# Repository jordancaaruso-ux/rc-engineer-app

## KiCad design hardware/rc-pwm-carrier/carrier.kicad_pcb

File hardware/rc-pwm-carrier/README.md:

# RC PWM Logger — Carrier Board (rev A)

Small carrier PCB for the **ESP32-S3-DevKitC-1** dev board. The devkit plugs into two
socket rows; the carrier provides receiver-rail power, PWM voltage dividers, and
servo-lead connectors. Replaces the loose-wire prototype in
`../rc-pwm-logger/PROTOTYPE_BUILD_PACKET.md` with a track-worthy, JLCPCB-assembled board.

**This is NOT the full custom board** — that project (`../rc-pwm-logger/V1.*`) is parked.
The carrier exists to prove the passive-tap concept and the data's value cheaply.

## Locked decisions (founder, 2026-07-18)

| Decision | Choice |
|---|---|
| Compute | ESP32-S3-DevKitC-1 (USB-C, WROOM-1 N8) — plugs in, never soldered |
| Power | From the receiver/BEC rail (5.5–8.4 V) via on-board buck to 5 V |
| Channels | 2 — steering + throttle/brake, standard 3-pin servo headers |
| Assembly | JLCPCB assembles everything incl. through-hole (founder does zero soldering) |
| Sessions | ~10 min target (dev-board internal flash is enough; no SD, no NOR) |

## Safety rule (inherited, non-negotiable)

**Listener only.** The carrier taps receiver PWM through series dividers; it is never in
the receiver→servo/ESC path. The car must drive identically with the logger present,
absent, unpowered, or rebooting. Servo Y-leads at the receiver provide the tap.

## Architecture

```
RX ch1 (Y-lead) ──► J2 servo header ──► R1 10k ──┬──► GPIO4 (J1 pin 4, steering)
                                            R2 15k ▼ GND
RX ch2 (Y-lead) ──► J3 servo header ──► R3 10k ──┬──► GPIO5 (J1 pin 5, throttle)
                                            R4 15k ▼ GND
J2/J3 + pins (BEC rail) ──► F1 PTC ──► D1 SS34 ──► U2 AP63205 buck (5 V) ──► D2 ──► devkit 5V pin
```

- Divider: 10 k series / 15 k to GND — 5 V rail → 3.0 V at GPIO (3.3 V-safe). Same values
  as the V1 design and the prototype packet.
- D2 (Schottky into the devkit 5 V pin) prevents fights when USB is plugged in while the
  carrier is powered — USB simply wins. Espressif lists the 5 V pin as a supported
  external power input (power sources are "mutually exclusive"; D2 makes simultaneous safe).
- Devkit's own USB-C stays exposed for flashing/bench; BLE for field offload.

## Key parts

| Ref | Part | Package | LCSC | Notes |
|---|---|---|---|---|
| U1 | ESP32-S3-DevKitC-1 sockets — 2× 1×22 female 2.54 mm | THT | pick at order time | Row spacing **22.86 mm** (official Espressif footprint, vendored) |
| U2 | AP63205WU-7 — 5 V / 2 A sync buck, 3.8–32 V in | TSOT-26 | C2071056 | + input cap, bootstrap cap, inductor (~6.8 µH), output caps per datasheet |
| F1 | PTC resettable fuse, ~1.1 A hold | 1812 | TBD (basic) | Receiver-rail inrush/fault protection |
| D1 | SS34 Schottky, reverse polarity | SMA | C8678 | Same as V1 |
| D2 | Schottky, 5 V feed to devkit | SMA/SOD-123 | TBD (basic) | ~0.3–0.45 V drop is fine (feeds devkit's own 3.3 V LDO) |
| R1–R4 | 10 k ×2, 15 k ×2 dividers | 0603 | basic | 1 % |
| J2, J3 | 3-pin male servo headers (JR: sig / + / GND) | THT 2.54 | pick at order time | Standard servo extension leads plug straight in |

Plus: 4× M3 mounting holes, flat underside (all parts topside) for servo-tape mounting.
Test pads on both divided signals + 5 V + GND.

## Vendored library files (`vendor/`)

- `ESP32-S3-DevKitC.kicad_mod` — official Espressif footprint (2 rows × 22, 22.86 mm apart)
- `Espressif.kicad_sym` — official symbol library (contains `ESP32-S3-DevKitC`)

Source: github.com/espressif/kicad-libraries @ main, fetched 2026-07-18.

## Pin map (devkit header pins, per Espressif user guide v1.1)

| Signal | Devkit pin | GPIO |
|---|---|---|
| Steering (divided) | J1 pin 4 | GPIO4 |
| Throttle (divided) | J1 pin 5 | GPIO5 |
| +5 V in (via D2) | J1 pin 21 | 5V |
| GND | J1 pin 22, J3 pins 1/21/22 | G |

Matches `firmware/rc-pwm-logger/src/board_pins.h` (`esp32-s3-devkit` board, GPIO4/GPIO5) —
**no firmware change needed.**

## Build phases

1. ✅ Research: pinout, row spacing, buck choice, official footprint vendored
2. ✅ Schematic (`carrier.kicad_sch`) → **ERC 0/0** (generated by `scripts/gen_schematic.py`;
   netlist verified pin-by-pin against design intent, 2026-07-18)
3. ✅ Layout + routing → **DRC 0 errors, 0 unconnected** (72×47 mm 2-layer,
   `scripts/gen_pcb.py`; 2 benign silk warnings from the intentional module overhang)
4. ✅ Fab exports → `output/jlcpcb/` (gerbers zip, BOM, CPL; `scripts/export_fab.py`)
5. ⬜ Founder uploads per `ORDER_GUIDE.md`, orders devkit from AU shop

## Pre-order gates

- [x] ERC: 0 errors (2026-07-19)
- [x] DRC: 0 errors, board outline on Edge.Cuts, 0 unconnected pads (2026-07-19)
- [x] Socket rows placed FROM the vendored Espressif footprint (22.86 mm by construction)
- [x] Divider junctions → GPIO4/GPIO5 verified in netlist + DRC connectivity
      (matches `board_pins.h` esp32-s3-devkit pins)
- [x] Servo header polarity on silkscreen (ST / TH + `S + -`)
- [x] BOM/CPL columns match JLCPCB template (16 placements, TPs/holes excluded)
- [ ] 4 BOM rows picked live in JLC's parts tool at upload time (15k R, PTC,
      pin headers, 1x22 sockets) — see `ORDER_GUIDE.md` step 5
- [ ] Placement preview eyeballed against `output/board-top.png` (diode stripes east)

## Firmware status (sibling project `firmware/rc-pwm-logger`)

2026-07-19: BLE offload rework (MTU-negotiated chunks up to 244 B, 3 ms gap —
~40-80× faster than the old 20 B + 8 ms) + `partitions_8mb_logger.csv`
(2 MB app / 5.9 MB LittleFS ≈ 55 min at 200 Hz). **Compiles clean**
(`py -3 -m platformio run`, flash 45.6%). Not yet flashed to hardware.

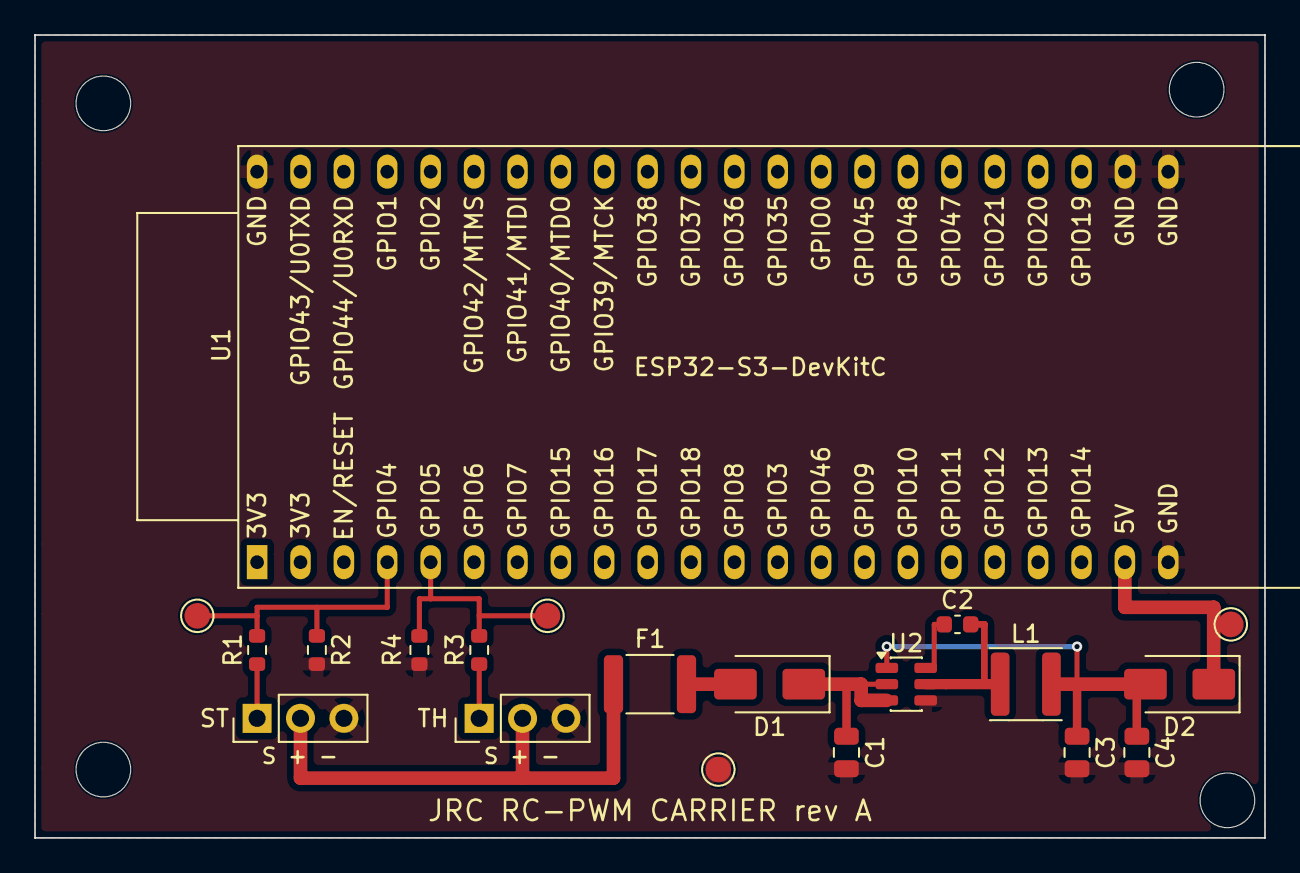
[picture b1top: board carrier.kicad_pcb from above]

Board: 2 copper layers, 72.0 x 47.0 mm, 24 parts (0 on the bottom side), 12 nets.

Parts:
C1, C3, C4: C_0805_2012Metric
C2: C_0603_1608Metric
D1, D2: D_SMA
F1: Fuse_1812_4532Metric
H1, H2, H3, H4: MountingHole_3.2mm_M3
J1, J2: PinHeader_1x03_P2.54mm_Vertical
L1: L_Sunlord_SWPA4030S
R1, R2, R3, R4: R_0603_1608Metric
TP1, TP2, TP3, TP4: TestPoint_Pad_D1.5mm
U1: ESP32-S3-DevKitC
U2: TSOT-23-6

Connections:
BST: C2.1, U2.6
GND: C1.2, C3.2, C4.2, J1.3, J2.3, R2.2, R4.2, TP4.1, U1.22, U1.23, U1.24, U1.44, U2.4
P5V_BUCK: C3.1, C4.1, D2.2, L1.2, U2.1
P5V_DK: D2.1, TP3.1, U1.21
ST_PWM_3V: R1.2, R2.1, TP1.1, U1.4
ST_PWM_RAW: J1.1, R1.1
SW: C2.2, L1.1, U2.5
TH_PWM_3V: R3.2, R4.1, TP2.1, U1.5
TH_PWM_RAW: J2.1, R3.1
VIN_F: D1.2, F1.2
VIN_PROT: C1.1, D1.1, U2.2, U2.3
VIN_RAW: F1.1, J1.2, J2.2

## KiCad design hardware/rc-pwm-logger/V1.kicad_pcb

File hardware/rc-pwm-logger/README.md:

# RC PWM logger (hardware)

In-car logger for **receiver PWM driver inputs**: **steering** and **throttle/brake** (two servo-style channels; throttle/brake is typically **one** ESC channel on surface cars).

KiCad is the **source of truth** for schematic and PCB. This folder holds the KiCad project (`.kicad_pro`, `.kicad_sch`, `.kicad_pcb`) once created, plus human-readable specs for Cursor reviews.

## Frozen decisions (rev A baseline)

| Topic | Choice |
|--------|--------|
| MCU | **ESP32-S3-WROOM-1** (or **N8** / **N8R2** variant per stock); **KiCad 10.x** |
| `VIN` (BEC / RX rail) | **5.5 V–8.5 V** recommended operating; design for **6–8.4 V** typical; include **fuse or PTC** + **reverse-polarity protection** |
| 3.3 V rail | **Synchronous buck** preferred (BLE + flash peaks); **LDO-only** acceptable only if thermal headroom verified |
| USB | **USB-C** (UFP); **5.1 kΩ** CC pulldowns; **Native USB-Serial/JTAG** on S3 if used, **or** **CH340C** UART bridge (pick one in schematic—do not orphan unused USB pins) |
| PWM sense | **High-impedance passive tap** from receiver PWM through a divider/protection network to **≤3.3 V** ESP32-safe levels (**non-inverted**); document divider ratio in `PINMUX.md` after calc |
| Passthrough | **2×** channels: receiver signal must reach ESC/servo by **direct copper pass-through or external Y harness**; the ESP32 must never regenerate or gate the control signal |
| Storage | **ESP32 module flash / LittleFS** as the rev A log buffer; **no microSD** on rev A (reduces mech + FAT risk; BLE offload to phone). Add external NOR only if flash capacity or endurance testing requires it |
| Sample rate target | **200 Hz** logged effective per channel (firmware); informs SPI burst / BLE chunk sizing later |
| BLE | **Phone offload after run** (buffer on device, bulk transfer); layout: **module antenna keepout** per Espressif datasheet |
| Fab | **2-layer**, **0603** passives default, **JLCPCB** + **LCSC** MPNs on BOM where possible |

## No-lag control requirement

The logger is a **listener**, not a controller. Throttle and steering PWM must still pass normally if the logger is unpowered, crashed, rebooting, or being reflashed. Validate the prototype by comparing receiver-to-ESC/servo pulse timing with and without the logger attached; a passive tap should add effectively **0 us** of delay.

## KiCad project setup

1. **File → New Project** → save **into this directory** (`hardware/rc-pwm-logger/`) so paths align with git.
2. Follow build order in [KICAD_PHASES.md](KICAD_PHASES.md).
3. After each phase: run ERC; paste errors or screenshots into Cursor with [REVIEW_CHECKLIST.md](REVIEW_CHECKLIST.md).
4. Before order: [FAB_CHECKLIST.md](FAB_CHECKLIST.md).

## Optional automation

See [OPTIONAL_MCP.md](OPTIONAL_MCP.md) for KiCad MCP (Cursor) — **optional**, not required for rev A.

## Firmware

Application code lives in [`firmware/rc-pwm-logger/`](../../firmware/rc-pwm-logger/) (PlatformIO skeleton). Hardware bring-up can proceed before firmware is complete.

## Changelog

See [CHANGELOG.md](CHANGELOG.md).

Made-with: Cursor

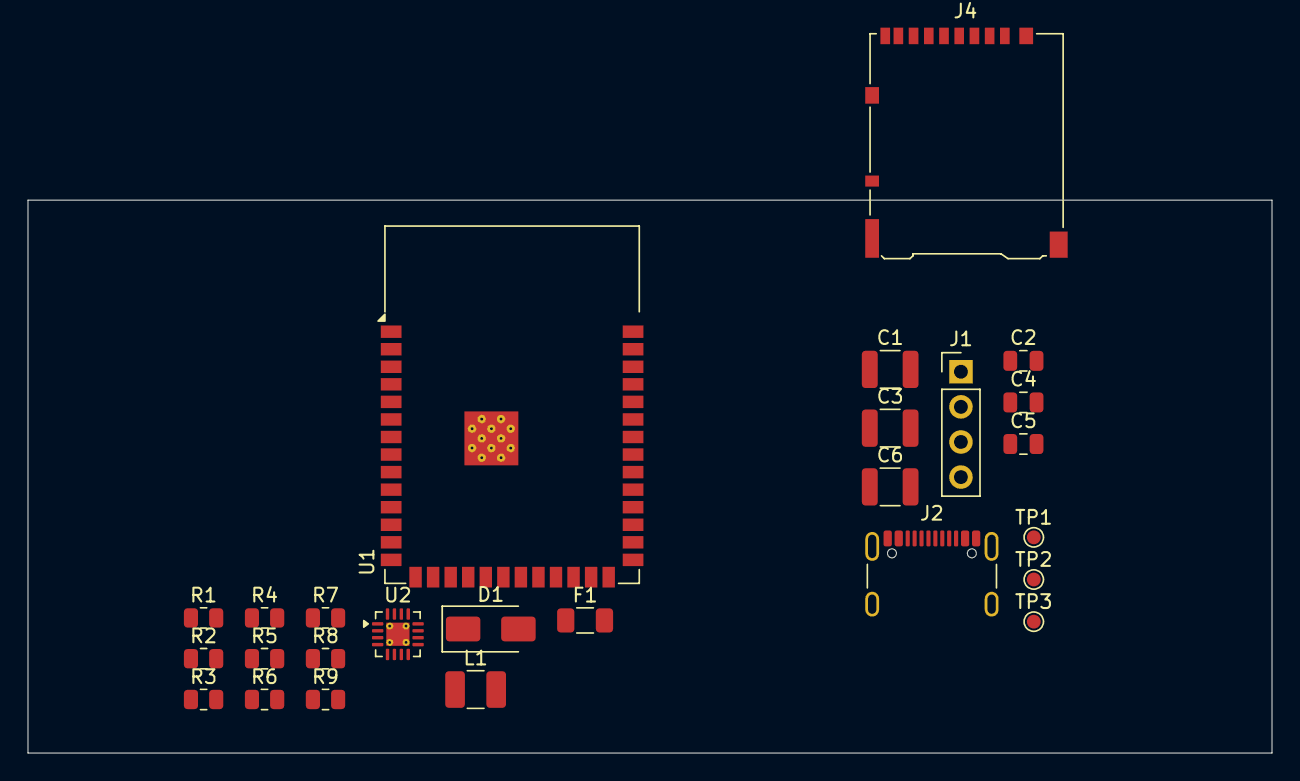
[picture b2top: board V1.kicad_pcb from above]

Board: 2 copper layers, 90.0 x 40.0 mm, 26 parts (0 on the bottom side), 12 nets, no tracks yet.

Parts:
C1: 10uF/25V; C_1210_3225Metric
C2, C4, C5: 100nF; C_0805_2012Metric
C3: 22uF/10V; C_1210_3225Metric
C6: 10uF; C_1210_3225Metric
D1: SS34; D_SMA
F1: 500mA; Fuse_1206_3216Metric
J1: RX_HARNESS; PinHeader_1x04_P2.54mm_Vertical
J2: USB4105-GF-A or equiv; USB_C_Receptacle_GCT_USB4105-xx-A_16P_TopMnt_Horizontal
J4: MicroSD; microSD_HC_Hirose_DM3AT-SF-PEJM5
L1: 2.2uH; L_1210_3225Metric_Pad1.42x2.65mm_HandSolder
R1, R2, R5, R6, R8: 10k; R_0805_2012Metric
R3, R4: 5.1k; R_0805_2012Metric
R7, R9: 15k; R_0805_2012Metric
TP1: U0TX; TestPoint_Pad_D1.0mm
TP2: U0RX; TestPoint_Pad_D1.0mm
TP3: GND; TestPoint_Pad_D1.0mm
U1: ESP32-S3-WROOM-1-N8; ESP32-S3-WROOM-1
U2: TPS62132RGTR; VQFN-16-1EP_3x3mm_P0.5mm_EP1.68x1.68mm_ThermalVias

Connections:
+3V3: J2.A1 (GND), J2.A12 (GND), J2.B1 (GND), J2.B12 (GND), J2.SH (SHIELD), J4.6 (VSS), L1.1 (1_1), R4.2, R5.2, TP2.1 (1_1), U1.1 (GND), U1.2 (3V3), U1.40 (GND), U1.41 (GND)
EN_CPU: R5.1, U1.9 (IO16)
unnamed: J1.3, R6.1
unnamed: J2.A5 (CC1), R3.1
unnamed: J2.B5 (CC2), R4.1
PWM_CH1: C1.1, C1.2, C2.1, C3.1, C3.2, C4.2, D1.1 (K), D1.2 (A), F1.1, F1.2, J1.2, R1.1, R1.2, R6.2, R7.1, R7.2, R8.2, R9.1, R9.2, U1.3 (EN)
SD_CLK: J4.5 (CLK), U1.38 (IO2)
SD_CMD: J4.7 (DAT0), U1.15 (IO3)
SD_CS: J4.8 (DAT1), U1.4 (IO4)
SD_MISO: J4.3 (CMD), U1.39 (IO1)
USB_DM: J2.A6 (D+), J2.B7 (D-), U1.13 (USB_D-)
USB_DP: J2.A7 (D-), J2.B6 (D+)
